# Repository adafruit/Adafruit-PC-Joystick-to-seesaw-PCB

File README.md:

## Adafruit PC Joystick to seesaw I2C Adapter - STEMMA QT / Qwiic PCB

<a href="http://www.adafruit.com/products/5753"><br/>
Click here to purchase one from the Adafruit shop</a>

PCB files for the Adafruit PC Joystick to seesaw I2C Adapter - STEMMA QT / Qwiic. 

Format is EagleCAD schematic and board layout
* https://www.adafruit.com/product/5753

### Description

Back in Ladyada's day, we used to have these big chunky PC joysticks that would plug into the back of your PC. No, not through USB, they had a DE-15 port and they'd go into the Game Port your sound effects card. Now, of course, we have tons of USB ports and quality audio is built into every computer. But what if you want to re-live your Commander Keen days?

This board has a 15 pin D-Sub socket port, that you can plug any classic PC joystick into. Onboard is a ATtiny816 helper chip that acts as a I2C peripheral using our 'seesaw' library. Two STEMMA QT ports mean you can plug this board in using a 4-pin JST SH cable to any microcontroller or microcomputer with I2C support and read the joystick X & Y plus the two buttons, even if your main chip doesn't have analog inputs. There's even a 5V power generator on-board since joysticks are expecting that voltage.

Great for converting old controllers without needing to cut any cables. We have example code for Arduino and CircuitPython / Python to make your next pew pew project a breeze.

Ships fully assembled and tested. If you prefer working on a breadboard, each order comes with a small piece of header. You'll need to solder the header onto the PCB, but it's fairly easy and takes only a few minutes even for a beginner. 

## DE-15 Connector Wiring

We suggest referring to the diagrams on [this page](https://allpinouts.org/pinouts/connectors/input_device/joystick-pc-gameport/) and on [Wikipedia](https://en.wikipedia.org/wiki/Game_port).

The original IBM Game Control Adapter manual is [here](https://www.minuszerodegrees.net/oa/OA%20-%20IBM%20Game%20Control%20Adapter.pdf).

### License

Adafruit invests time and resources providing this open source design, please support Adafruit and open-source hardware by purchasing products from [Adafruit](https://www.adafruit.com)!

Designed by Limor Fried/Ladyada for Adafruit Industries.

Creative Commons Attribution/Share-Alike, all text above must be included in any redistribution. 
See license.txt for additional details.

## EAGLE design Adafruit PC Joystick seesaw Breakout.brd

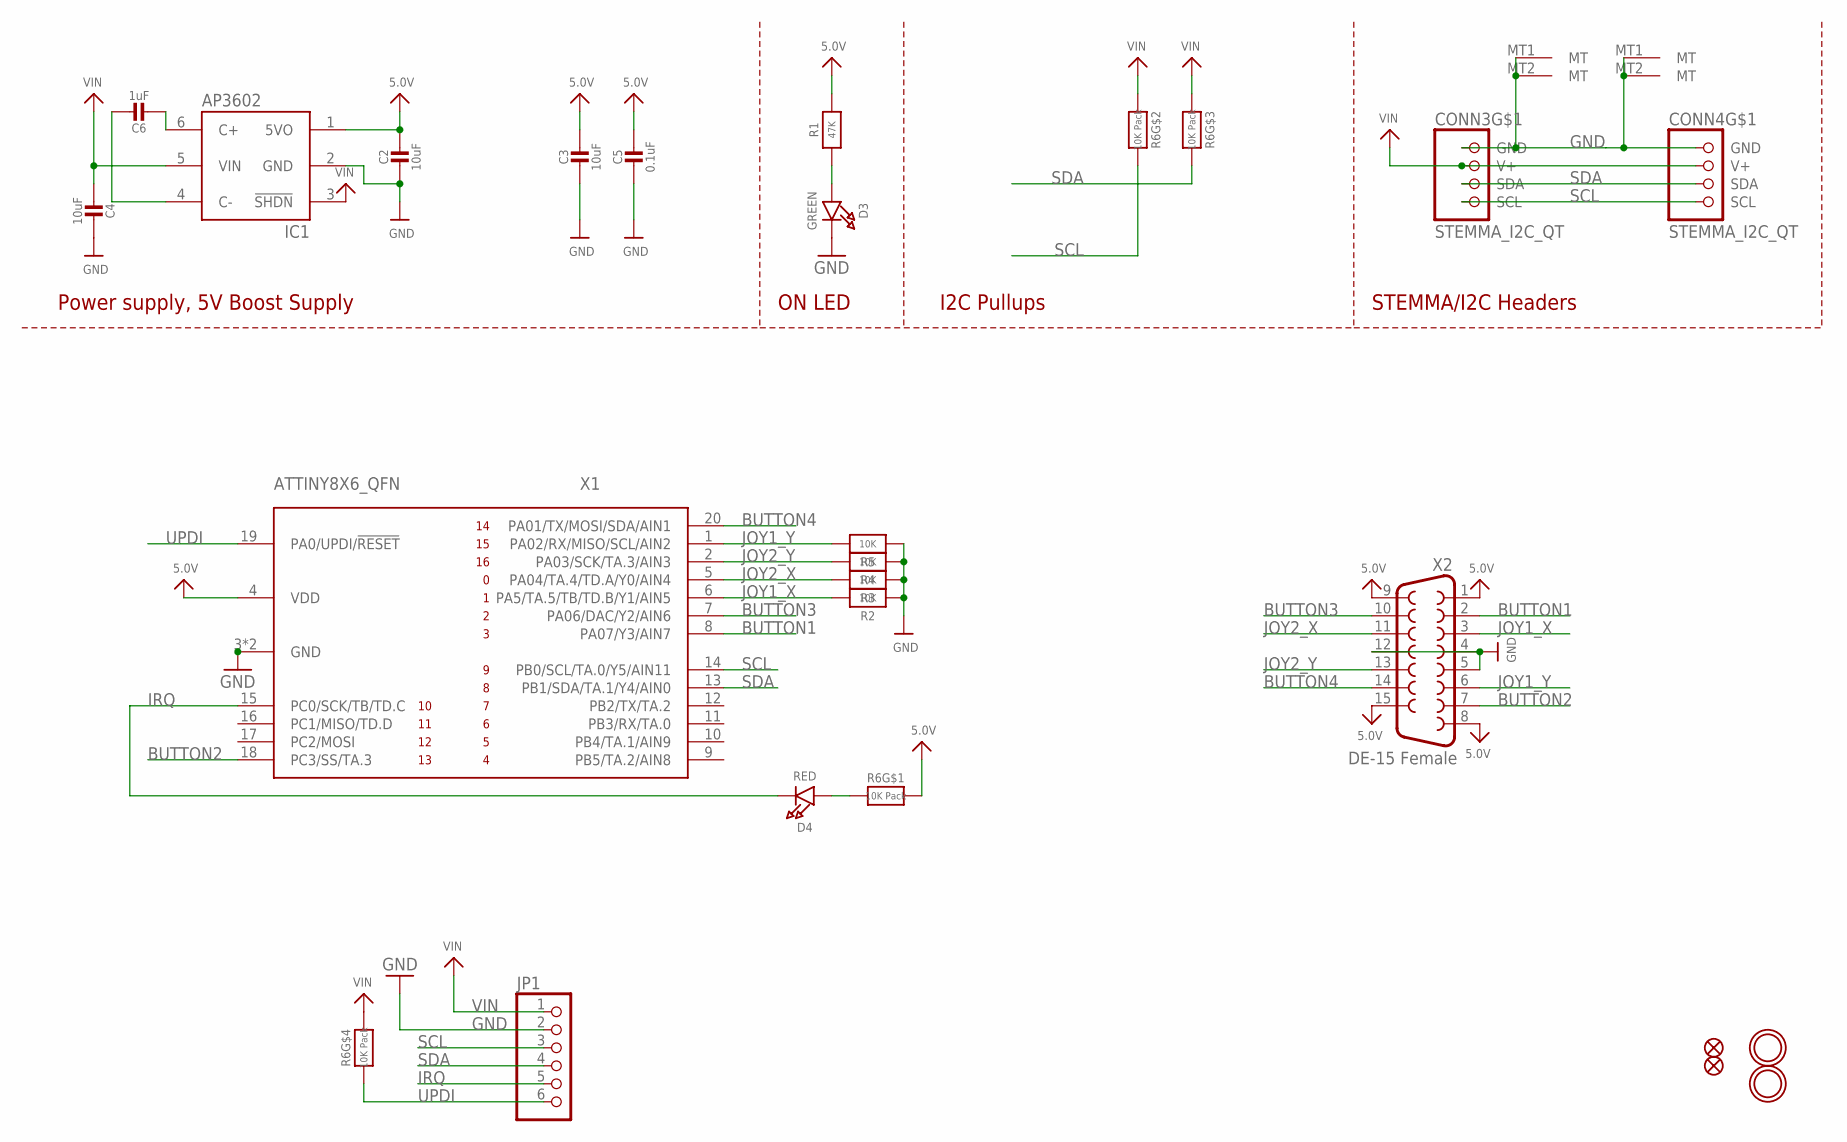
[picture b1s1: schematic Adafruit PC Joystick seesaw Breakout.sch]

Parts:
C2, C3, C4: 10uF; 0805-NO
C5: 0.1uF; 0603-NO
C6: 1uF; 0603-NO
CONN3, CONN4: STEMMA_I2C_QT; JST_SH4
D3: GREEN; CHIPLED_0603_NOOUTLINE
D4: RED; CHIPLED_0603_NOOUTLINE
FID1, FID2: FIDUCIAL_1MM
IC1: AP3602; SOT23-6
JP1: HEADER-1X670MIL; 1X06_ROUND_70
R1: 47K; 0603-NO
R2, R3, R4, R5: 10K; 0603-NO
R6: 10K Pack; RESPACK_4X0603
U$6, U$18: MOUNTINGHOLE2.5; MOUNTINGHOLE_2.5_PLATED
X1: ATTINY8X6_QFN; QFN20_3MM
X2: DE-15 Female; F15H

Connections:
5.0V: C2.1, C3.1, C5.1, IC1.1 (5VO), R1.2, R6.8 (2), X1.4 (VDD), X2.1, X2.8, X2.9, X2.15
BUTTON1: X1.8 (PA07/Y3/AIN7), X2.2
BUTTON2: X1.18 (PC3/SS/TA.3), X2.7
BUTTON3: X1.7 (PA06/DAC/Y2/AIN6), X2.10
BUTTON4: X1.20 (PA01/TX/MOSI/SDA/AIN1), X2.14
GND: C2.2, C3.2, C4.2, C5.2, CONN3.1 (GND), CONN3.MT1 (MT), CONN3.MT2 (MT), CONN4.1 (GND), CONN4.MT1 (MT), CONN4.MT2 (MT), D3.C, IC1.2 (GND), JP1.2, R2.1, R3.1, R4.1, R5.1, X1.3 (GND), X1.PAD (GND), X2.4, X2.5, X2.12
IRQ: D4.C, JP1.5, X1.15 (PC0/SCK/TB/TD.C)
JOY1_X: R2.2, X1.6 (PA5/TA.5/TB/TD.B/Y1/AIN5), X2.3
JOY1_Y: R5.2, X1.1 (PA02/RX/MISO/SCL/AIN2), X2.6
JOY2_X: R3.2, X1.5 (PA04/TA.4/TD.A/Y0/AIN4), X2.11
JOY2_Y: R4.2, X1.2 (PA03/SCK/TA.3/AIN3), X2.13
unnamed: D3.A, R1.1
unnamed: C6.2, IC1.6 (C+)
unnamed: C6.1, IC1.4 (C-)
unnamed: D4.A, R6.1
SCL: CONN3.4 (SCL), CONN4.4 (SCL), JP1.3, R6.7 (2), X1.14 (PB0/SCL/TA.0/Y5/AIN11)
SDA: CONN3.3 (SDA), CONN4.3 (SDA), JP1.4, R6.6 (2), X1.13 (PB1/SDA/TA.1/Y4/AIN0)
UPDI: JP1.6, R6.4 (1), X1.19 (PA0/UPDI/!RESET)
VIN: C4.1, CONN3.2 (V+), CONN4.2 (V+), IC1.3 (!SHDN), IC1.5 (VIN), JP1.1, R6.2 (1), R6.3 (1), R6.5 (2)

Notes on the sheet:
I2C Pullups
STEMMA/I2C Headers
ON LED
Power supply, 5V Boost Supply

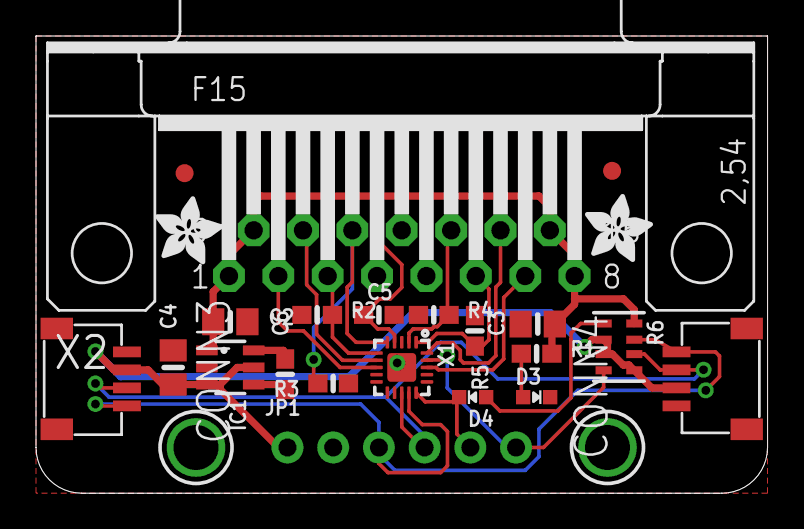
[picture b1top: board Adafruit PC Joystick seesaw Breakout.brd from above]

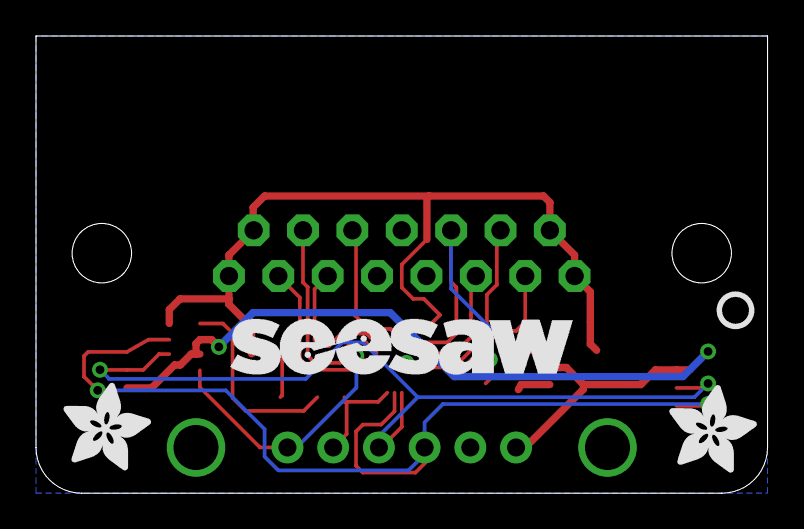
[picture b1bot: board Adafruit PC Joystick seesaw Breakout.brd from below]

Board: 2 copper layers, 40.6 x 25.4 mm, 41 parts (8 on the bottom side), 19 nets.

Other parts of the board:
PLABEL0: PLABEL0
PLABEL1: PLABEL1
PLABEL2: PLABEL2
PLABEL3: PLABEL3
PLABEL4: PLABEL4
PLABEL5: PLABEL5
PLABEL6: PLABEL6
PLABEL7: PLABEL7
PLABEL8: PLABEL8
PLABEL9: PLABEL9
PLABEL10: PLABEL10
PLABEL11: PLABEL11
U$7: SEESAW_LOGO
U$12: PCBFEAT-REV-040
U$20, U$32: ADAFRUIT_5MM
U$30, U$31: ADAFRUIT_3.5MM

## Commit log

2023-08-07 adding cookiecutter output

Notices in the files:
parts and their libraries:
microbuilder: This work is placed in the public domain, and may be freely used for commercial and non-commercial work with the following conditions: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
